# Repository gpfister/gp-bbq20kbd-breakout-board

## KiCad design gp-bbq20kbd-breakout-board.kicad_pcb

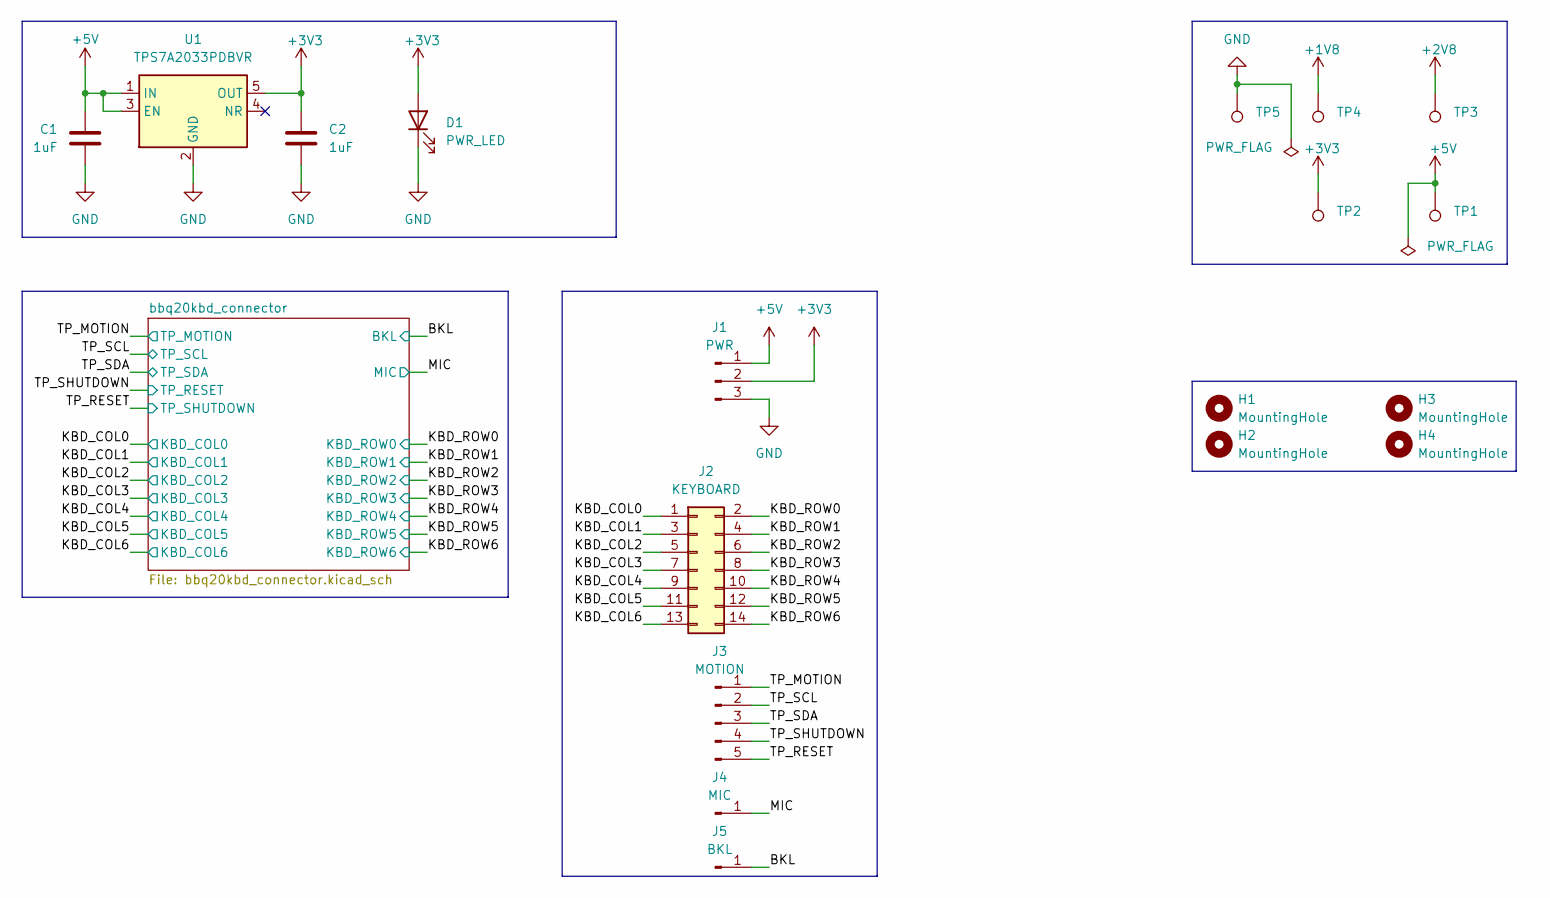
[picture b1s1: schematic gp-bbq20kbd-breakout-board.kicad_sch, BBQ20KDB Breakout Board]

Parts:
C1, C2: 1uF; C_0603_1608Metric
D1: PWR_LED; LED_0603_1608Metric
H1, H2, H3, H4: MountingHole; MountingHole_2.7mm_M2.5
J1: PWR; PinHeader_1x03_P2.54mm_Vertical
J2: KEYBOARD; PinHeader_2x07_P2.54mm_Vertical
J3: MOTION; PinHeader_1x05_P2.54mm_Vertical
J4: MIC; PinHeader_1x01_P2.54mm_Vertical
J5: BKL; PinHeader_1x01_P2.54mm_Vertical
TP1, TP2, TP3, TP4, TP5: TestPoint_Pad_D1.0mm
U1: TPS7A2033PDBVR; SOT-23-5

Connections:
+1V8: TP4.1; also elsewhere on the board
+2V8: TP3.1; also elsewhere on the board
+3V3: C2.1, D1.2 (A), J1.2, TP2.1, U1.5 (OUT); also elsewhere on the board
+5V: C1.1, J1.1, TP1.1, U1.1 (IN), U1.3 (EN)
/KBD_BKL: J5.1; also elsewhere on the board
/KBD_COL0: J2.1; also elsewhere on the board
/KBD_COL1: J2.2; also elsewhere on the board
/KBD_COL2: J2.3; also elsewhere on the board
/KBD_COL3: J2.4; also elsewhere on the board
/KBD_COL4: J2.5; also elsewhere on the board
/KBD_COL5: J2.6; also elsewhere on the board
/KBD_COL6: J2.7; also elsewhere on the board
/KBD_ROW0: J2.8; also elsewhere on the board
/KBD_ROW1: J2.9; also elsewhere on the board
/KBD_ROW2: J2.10; also elsewhere on the board
/KBD_ROW3: J2.11; also elsewhere on the board
/KBD_ROW4: J2.12; also elsewhere on the board
/KBD_ROW5: J2.13; also elsewhere on the board
/KBD_ROW6: J2.14; also elsewhere on the board
/MIC: J4.1; also elsewhere on the board
/TP_MOTION: J3.4; also elsewhere on the board
/TP_RESET: J3.5; also elsewhere on the board
/TP_SCL: J3.3; also elsewhere on the board
/TP_SDA: J3.2; also elsewhere on the board
/TP_SHUTDOWN: J3.1; also elsewhere on the board
GND: C1.2, C2.2, D1.1 (K), J1.3, TP5.1, U1.2 (GND); also elsewhere on the board

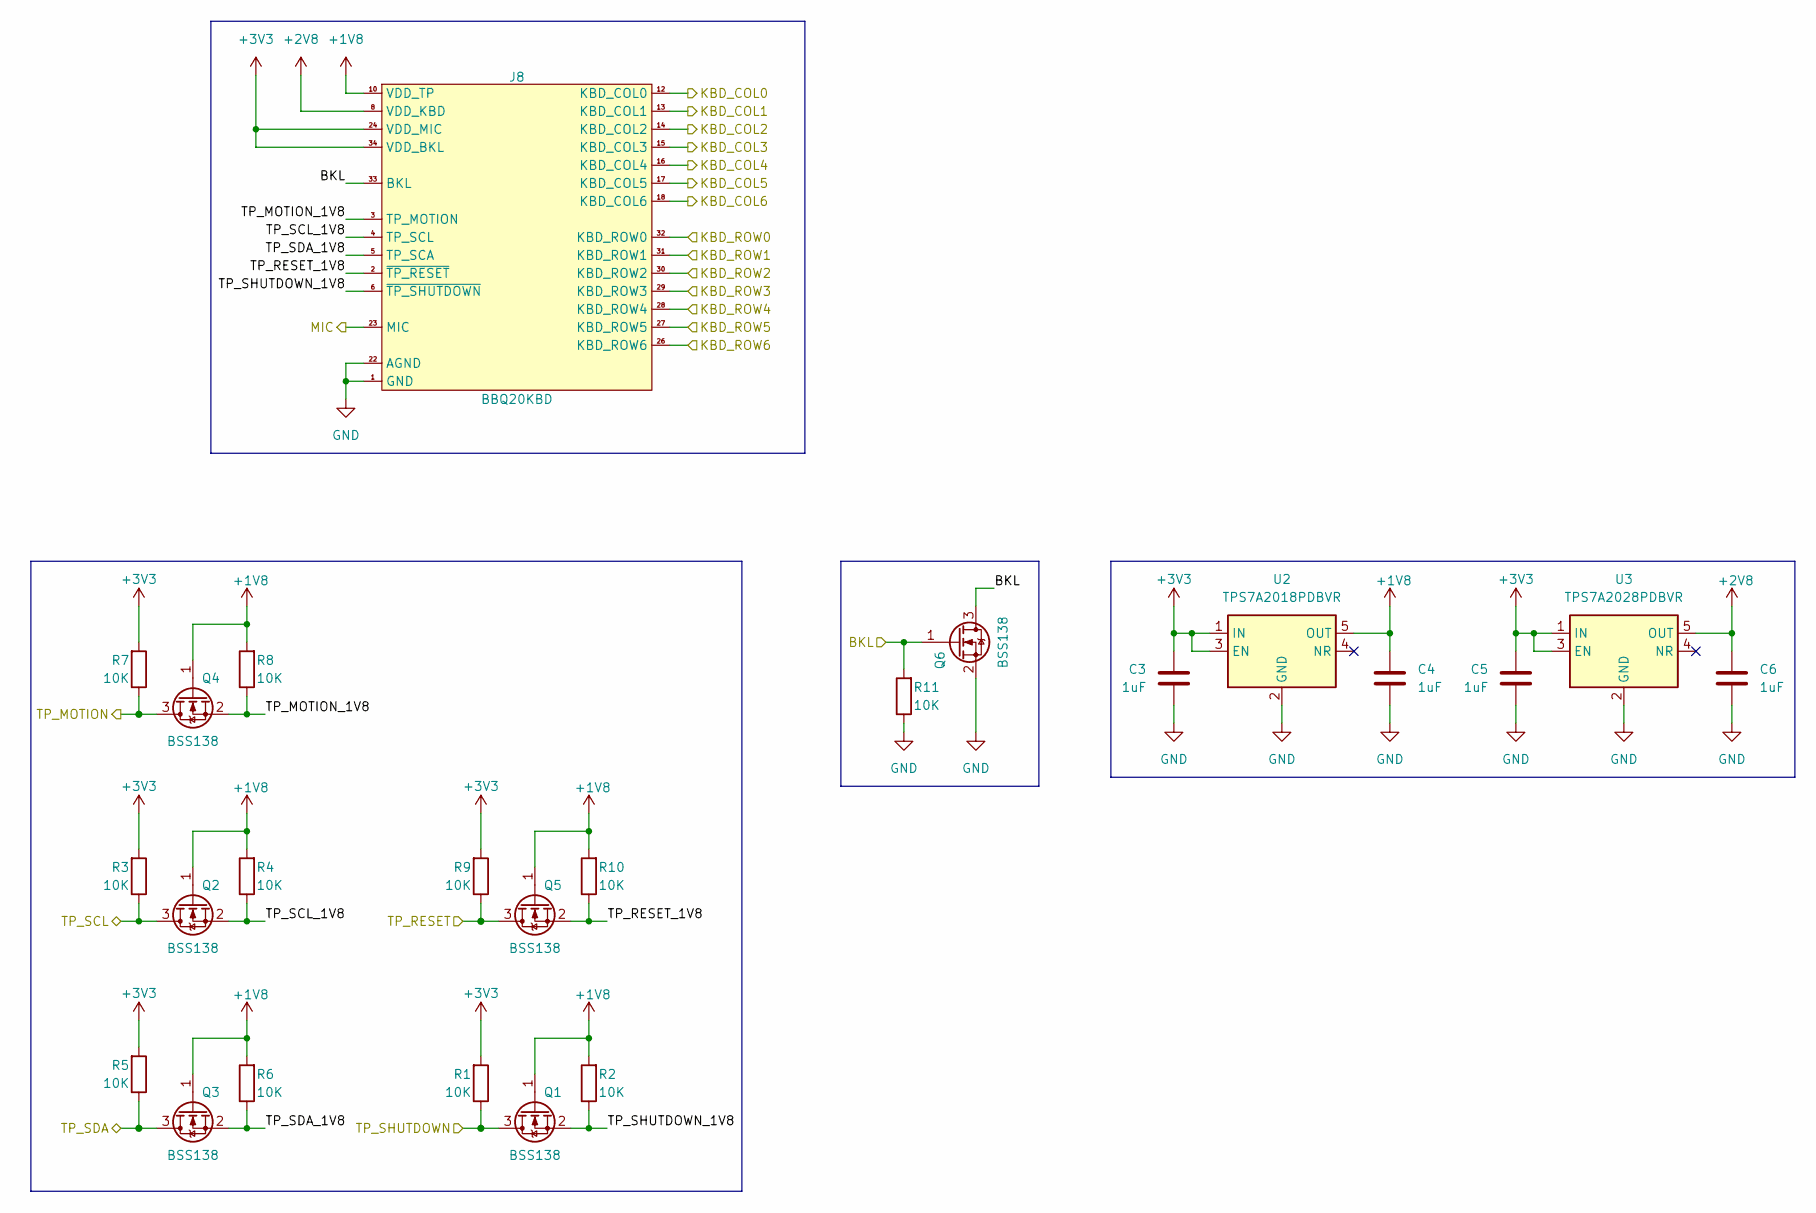
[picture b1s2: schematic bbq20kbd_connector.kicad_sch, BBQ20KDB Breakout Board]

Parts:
C3, C4, C5, C6: 1uF; C_0603_1608Metric
J8: BBQ20KBD; Hirose_BM20B0.8-40DS-0.4V
Q1, Q2, Q3, Q4, Q5, Q6: BSS138; SOT-23; LCSC C112239
R1, R2, R3, R4, R5, R6, R7, R8, R9, R10, R11: 10K; R_0603_1608Metric
U2: TPS7A2018PDBVR; SOT-23-5
U3: TPS7A2028PDBVR; SOT-23-5

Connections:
+1V8: C4.1, J8.10 (VDD_TP), Q1.1 (G), Q2.1 (G), Q3.1 (G), Q4.1 (G), Q5.1 (G), R2.2, R4.2, R6.2, R8.2, R10.2, U2.5 (OUT); also elsewhere on the board
+2V8: C6.1, J8.8 (VDD_KBD), U3.5 (OUT); also elsewhere on the board
+3V3: C3.1, C5.2, J8.24 (VDD_MIC), J8.34 (VDD_BKL), R1.2, R3.2, R5.2, R7.2, R9.2, U2.1 (IN), U2.3 (EN), U3.1 (IN), U3.3 (EN); also elsewhere on the board
/KBD_BKL: Q6.1 (G), R11.2; also elsewhere on the board
/KBD_COL0: J8.12 (KBD_COL0); also elsewhere on the board
/KBD_COL1: J8.13 (KBD_COL1); also elsewhere on the board
/KBD_COL2: J8.14 (KBD_COL2); also elsewhere on the board
/KBD_COL3: J8.15 (KBD_COL3); also elsewhere on the board
/KBD_COL4: J8.16 (KBD_COL4); also elsewhere on the board
/KBD_COL5: J8.17 (KBD_COL5); also elsewhere on the board
/KBD_COL6: J8.18 (KBD_COL6); also elsewhere on the board
/KBD_ROW0: J8.32 (KBD_ROW0); also elsewhere on the board
/KBD_ROW1: J8.31 (KBD_ROW1); also elsewhere on the board
/KBD_ROW2: J8.30 (KBD_ROW2); also elsewhere on the board
/KBD_ROW3: J8.29 (KBD_ROW3); also elsewhere on the board
/KBD_ROW4: J8.28 (KBD_ROW4); also elsewhere on the board
/KBD_ROW5: J8.27 (KBD_ROW5); also elsewhere on the board
/KBD_ROW6: J8.26 (KBD_ROW6); also elsewhere on the board
/MIC: J8.23 (MIC); also elsewhere on the board
/TP_MOTION: Q4.3 (D), R7.1; also elsewhere on the board
/TP_RESET: Q5.3 (D), R9.1; also elsewhere on the board
/TP_SCL: Q3.3 (D), R5.1; also elsewhere on the board
/TP_SDA: Q2.3 (D), R3.1; also elsewhere on the board
/TP_SHUTDOWN: Q1.3 (D), R1.1; also elsewhere on the board
/bbq20kbd_connector/BKL: J8.33 (BKL), Q6.3 (D)
/bbq20kbd_connector/TP_MOTION_1V8: J8.3 (TP_MOTION), Q4.2 (S), R8.1
/bbq20kbd_connector/TP_RESET_1V8: J8.2 (~TP_RESET), Q5.2 (S), R10.1
/bbq20kbd_connector/TP_SHUTDOWN_1V8: J8.6 (~TP_SHUTDOWN), Q1.2 (S), R2.1
GND: C3.2, C4.2, C5.1, C6.2, J8.1 (GND), J8.22 (AGND), Q6.2 (S), R11.1, U2.2 (GND), U3.2 (GND); also elsewhere on the board

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
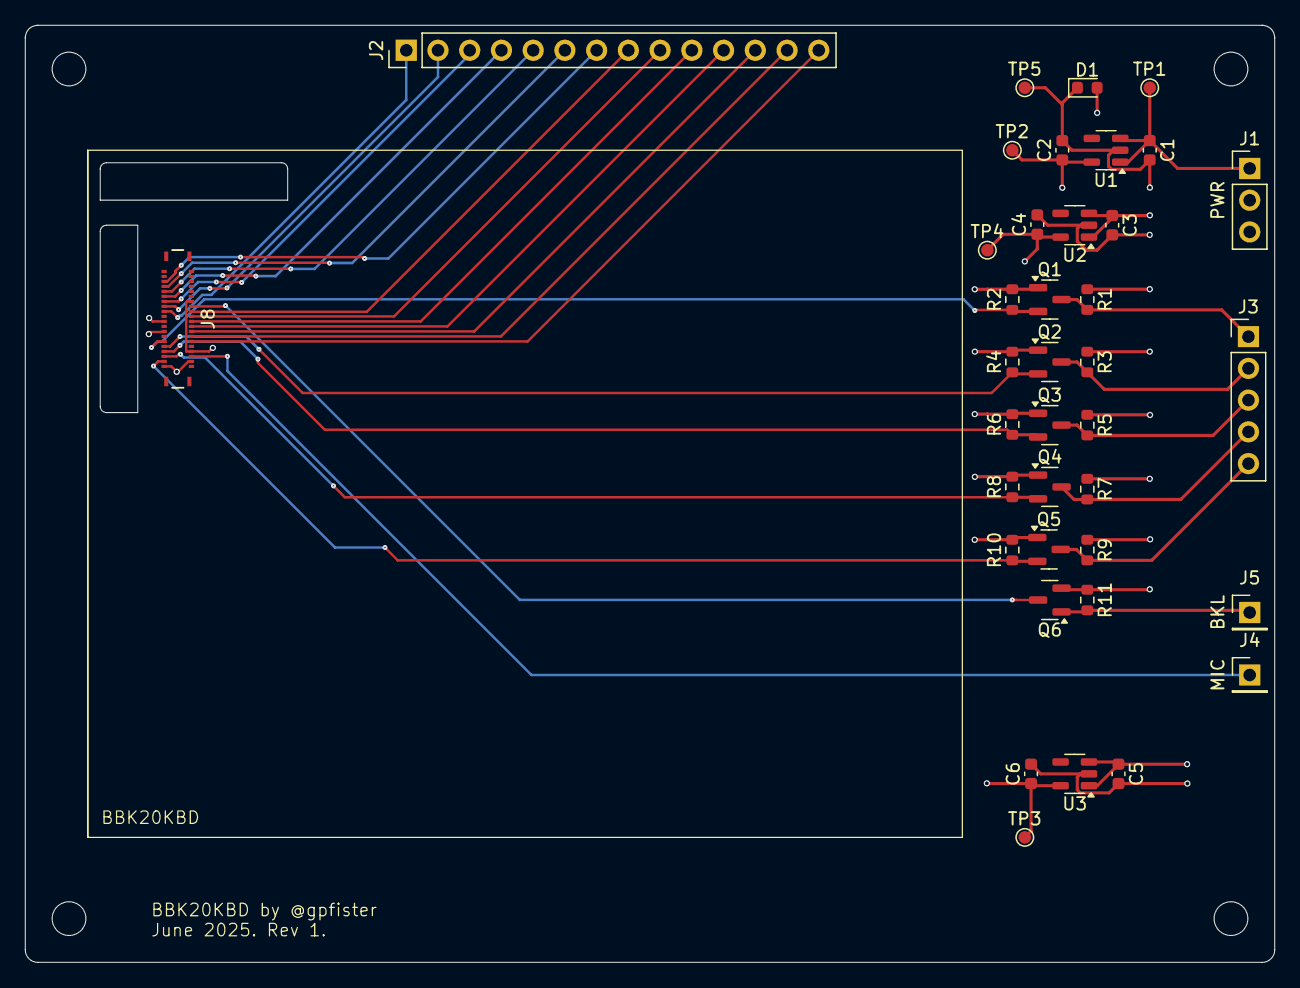
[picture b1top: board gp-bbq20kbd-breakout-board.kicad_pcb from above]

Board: 4 copper layers, 100.0 x 75.0 mm, 42 parts (0 on the bottom side), 32 nets.

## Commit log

2025-06-22 Begin PCB
2025-06-27 Version 1
2025-06-27 Version 1 (#1)
2025-07-04 Update gerbers
2025-07-04 Update gerbers (#2)

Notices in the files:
bbq20kbd_connector.kicad_sch:
Copyright (c) 2025, Greg PFISTER. CERN Open Hardware Licence v1.2.
